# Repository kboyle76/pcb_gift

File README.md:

# pcb_gift

This is a soldering kit for to be distributed at the Playa Circuit Booogie Camp at Burning Man 2017. Our goal was to design a soldering kit that does something a little bit more interesting than simply blinking lights while still costing less than a few dollars each. Only one color LED is initally lit after assembling the kit, and users must find another person to "share" their color with and receive new colors in return to light up the rest of the LEDs! Each device can only receive one color from each other device, and communication happens using infrared light.

### SMT Pre-assembly Notes
The surface mount components will be pre-populated to facilitate assembly at the Playa.
- The surface mount battery holders are a bit weak and tend to pop off the circuit board, sometimes bringing the pad with them. You may want to further secure them with a dab of epoxy.
- For aesthetic reasons, surface mount component names are not included in the bottom silkscreen. The component locations are shown below for your convenience.

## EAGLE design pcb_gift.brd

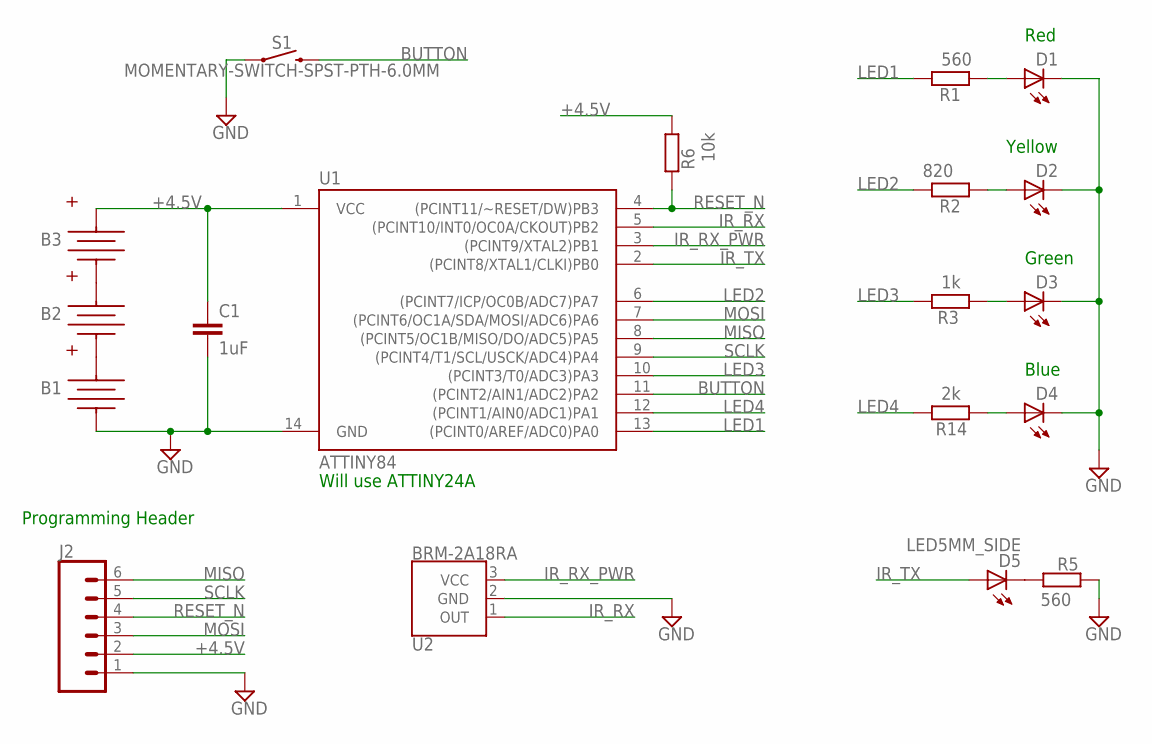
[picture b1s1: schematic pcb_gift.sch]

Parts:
B1, B2, B3: KEYSTONE_2996
C1: 1uF; C0805
D1, D2, D3, D4: LED5MM
D5: LED5MM_SIDE
J2: CONN_061.27MM; 1X06_1.27MM
R1, R5: 560; R0805
R2: 820; R0805
R3: 1k; R0805
R6: 10k; R0805
R14: 2k; R0805
S1: MOMENTARY-SWITCH-SPST-PTH-6.0MM; TACTILE_SWITCH_PTH_6.0MM
U1: ATTINY84; SO14
U2: BRM-2A18RA; BRM-2508

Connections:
+4.5V: B3.POSA (POS), B3.POSB (POS), C1.1, J2.2, R6.2, U1.1 (VCC)
BUTTON: S1.3 (2), U1.11 ((PCINT2/AIN1/ADC2)PA2)
GND: B1.NEG, C1.2, D1.K (C), D2.K (C), D3.K (C), D4.K (C), J2.1, R5.1, S1.1, U1.14 (GND), U2.2 (GND)
IR_RX: U1.5 ((PCINT10/INT0/OC0A/CKOUT)PB2), U2.1 (OUT)
IR_RX_PWR: U1.3 ((PCINT9/XTAL2)PB1), U2.3 (VCC)
IR_TX: D5.A, U1.2 ((PCINT8/XTAL1/CLKI)PB0)
LED1: R1.1, U1.13 ((PCINT0/AREF/ADC0)PA0)
LED2: R2.1, U1.6 ((PCINT7/ICP/OC0B/ADC7)PA7)
LED3: R3.1, U1.10 ((PCINT3/T0/ADC3)PA3)
LED4: R14.1, U1.12 ((PCINT1/AIN0/ADC1)PA1)
MISO: J2.6, U1.8 ((PCINT5/OC1B/MISO/DO/ADC5)PA5)
MOSI: J2.3, U1.7 ((PCINT6/OC1A/SDA/MOSI/ADC6)PA6)
unnamed: D1.A, R1.2
unnamed: B1.POSA (POS), B1.POSB (POS), B2.NEG
unnamed: B2.POSA (POS), B2.POSB (POS), B3.NEG
unnamed: D4.A, R14.2
unnamed: D3.A, R3.2
unnamed: D2.A, R2.2
unnamed: D5.K (C), R5.2
RESET_N: J2.4, R6.1, U1.4 ((PCINT11/~RESET/DW)PB3)
SCLK: J2.5, U1.9 ((PCINT4/T1/SCL/USCK/ADC4)PA4)

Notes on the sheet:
Will use ATTINY24A
Programming Header
Red
Yellow
Green
Blue

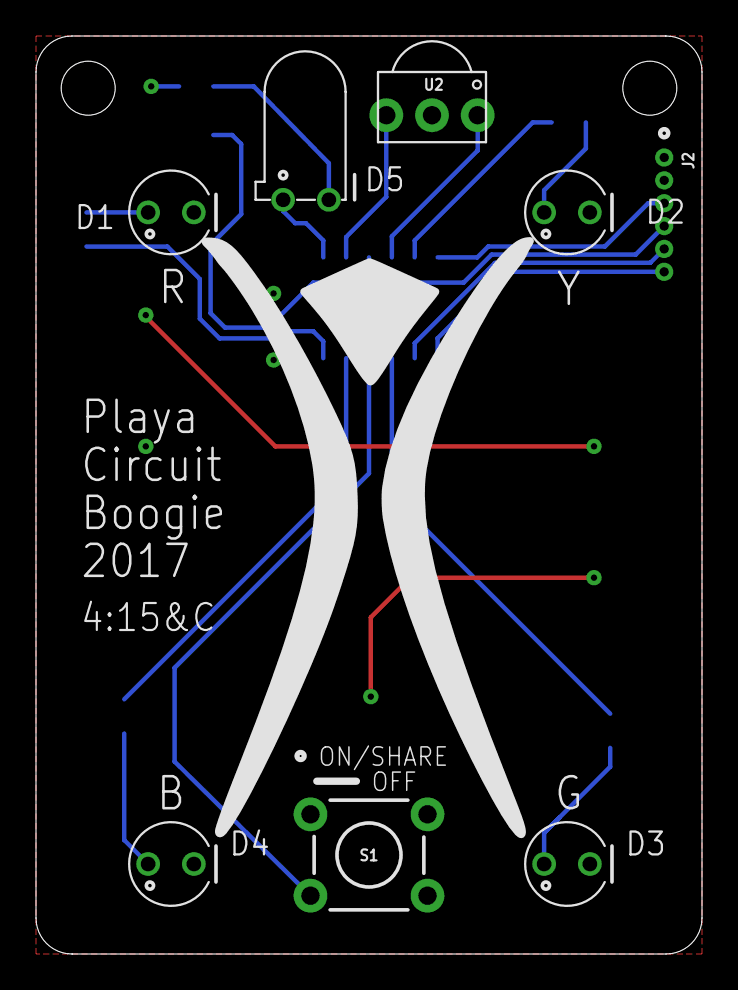
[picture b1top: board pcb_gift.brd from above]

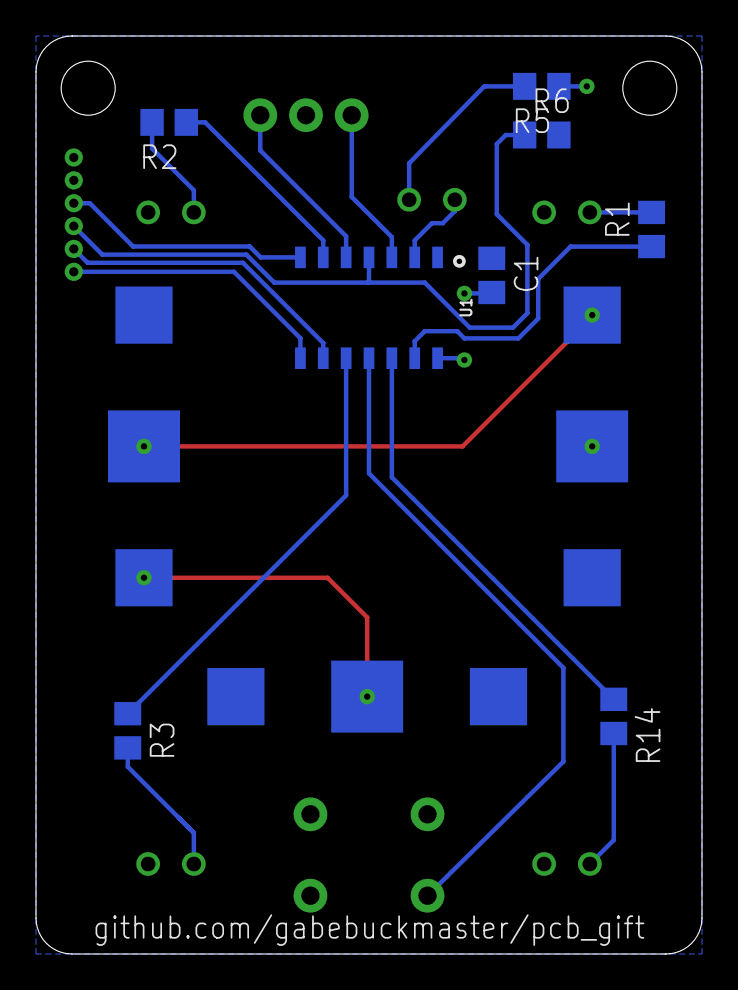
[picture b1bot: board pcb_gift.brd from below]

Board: 2 copper layers, 37.0 x 51.0 mm, 19 parts (11 on the bottom side), 21 nets.

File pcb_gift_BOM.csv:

Reference,Quantity,Description,Manufacturer,Part Number,Cost @ qty 100,Extended cost,Notes
U1,1,"8 bit microcontroller -12 GPIO, 14 SOIC",Microchip,ATTINY44A-SSU,0.618,61.8,Digikey
U2,1,38 kHz IR receiver,Vishay,TSOP38338,0.6,60,Digikey
C1,1,1uF 0805 ceramic capacitor X5R 6.3V,Generic,,0.0093,0.93,Digikey
S1,1,Tactile pushbutton,Generic,,0.04,8,Aliexpress
"R1, R5",2,5% 0805 Resistor 560 Ohms,Generic,,0.0067,1.34,Digikey
R2,1,5% 0805 Resistor 820 Ohms,Generic,,0.0067,0.67,Digikey
R3,1,5% 0805 Resistor 1.2k Ohms,Generic,,0.0067,0.67,Digikey
R4,1,5% 0805 Resistor 680 Ohms,Generic,,0.0067,0.67,Digikey
R6,1,5% 0805 Resistor 10k Ohms,Generic,,0.0067,0.67,Digikey
D1,1,5mm Red Led,Generic,,0.0181,1.81,Aliexpress
D2,1,5mm Yellow Led,Generic,,0.0181,1.81,Aliexpress
D3,1,5mm Green Led,Generic,,0.0181,1.81,Aliexpress
D4,1,5mm Blue Led,Generic,,0.0181,1.81,Aliexpress
D5,1,IR LED transmitter,Generic,,0.0181,1.81,Aliexpress
B1-3,3,Battery holder,Keystone,2996,0.20492,61.476,Digikey
N/A,3,LR44 battery,,,0.0788,23.64,Amazon

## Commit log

2017-07-26 Initial commit
    Board and schematic are finalized for this revision. Firmware still
    needs to be updated for this version of the PCB.
2017-07-26 Created README
2017-07-26 Fixed gerber file names
    Gerbers still had an old file name and have now been updated.
2017-08-08 updated code for new revision and cleaned things up
    - added bom
    - updated firmware for this version
    - firmware has deeper sleep mode
    - added scripts to compile/upload to board
    - added .gitignore
    - updated readme
2017-08-08 fixed image width in readme
    hopefully
2017-08-08 Update image sizes (again)
    Attempt #2 to fix the image sizes in README.md
2017-08-30 Adding instructions
    Adds pdf and powerpoint version of instruction sheet showing assembly and operation.

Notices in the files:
parts and their libraries:
SparkFun-Switches: Licensing: Creative Commons ShareAlike 4.0 International - https://creativecommons.org/licenses/by-sa/4.0
